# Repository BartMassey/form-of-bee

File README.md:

# Form Of Bee
Copyright © 2015 Bart Massey

This HW is a SOIC-16 ZIF-socket programming board for the
EFM8BB1. It is really simple: it has a socket for the USB
debugger, the ZIF socket, and an LED and speaker to indicate
that the board was programmed correctly. The layout is
deliberately single-sided through-hole to ease construction.

This project is part of the
*[Desert Lizard](http:/github.com/DesertLizard)* project, an
open-hardware open-source beginner e-jewelry and
construction tutorial project!

For details and current status, please see our GitHub
[wiki](http://github.com/DesertLizard/LizardBoard/wiki).

## License

The hardware design and source code for this project is
available under the MIT License. See the file COPYING in
this distribution for license terms.

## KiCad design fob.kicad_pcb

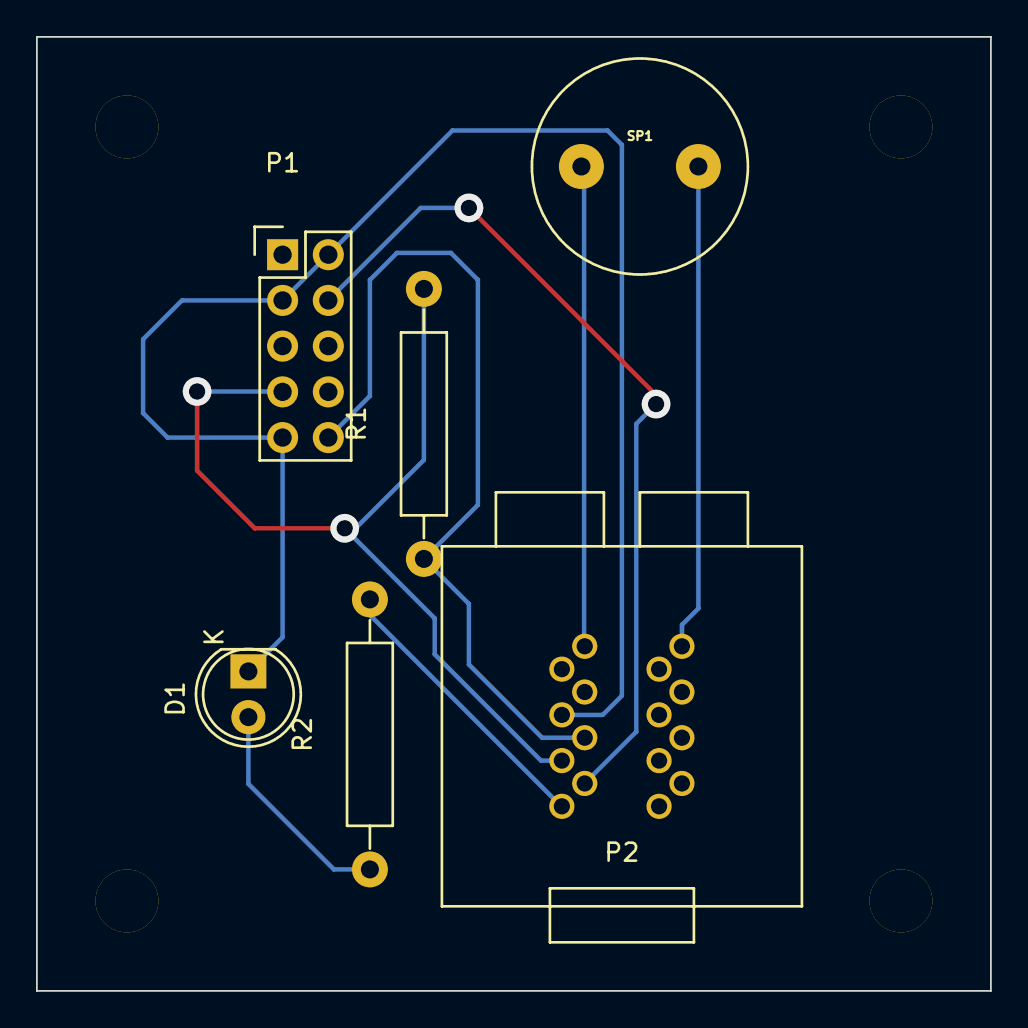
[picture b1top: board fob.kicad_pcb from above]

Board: 2 copper layers, 53.0 x 53.0 mm, 6 parts (0 on the bottom side), 8 nets.

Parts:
D1: LED RED; LED-5MM
P1: SW DBG; Pin_Header_Straight_2x05
P2: SOIC16-ZIF; WAVESHARE_FP-16-1.27-05
R1: 10K; Resistor_Horizontal_RM15mm
R2: 51; Resistor_Horizontal_RM15mm
SP1: SPEAKER; PUI-AT-1224-TWT-5V-2-R

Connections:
GND: D1.1, P1.2, P1.3, P1.9, P2.4
unnamed: D1.2, R2.1
unnamed: P1.4, P2.7
unnamed: P1.7, P2.6, R1.2
unnamed: P2.1, SP1.1
unnamed: P2.8, R2.2
unnamed: P2.16, SP1.2
VDD: P1.10, P2.5, R1.1

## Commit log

2015-08-21 EFM8BB1 ZIF programmer in KiCAD
2015-08-26 fixed waveshare footprint bug and did relayout
2015-08-26 got version 1.1 ready to cut
2015-08-26 fixed things found during PCB routing; XXX ZIF footprint is still wrong
2015-08-27 finished final cut version that is do-or-die; parts fit

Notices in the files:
fob.kicad_pcb:
Copyright 2015 Bart Massey
